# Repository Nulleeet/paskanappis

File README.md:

# paskanäppis
60%(ish)keyboard with ISO kc_nubs and f-row - so its really like 70% or 75%, or between, I dont know. I call it either paskanäppis or 60ish.

This is my learning opportunity to make and design my own keyboard.
Planning to use [kicad](https://www.kicad.org), [qmk](https://qmk.fm), [via](https://www.caniusevia.com) and/or [vial](https://get.vial.today) and [Keyboard PCB Builder](https://kb.xyz.is) and some 3d software (still planning what to use), and 3dprint case, for starters.
Maybe use [plate & case builder](http://builder.swillkb.com) to make acrylic case?

I tried already earlier to do this without Promicro and Elite-C, but I failed it and now the files are gone due to my hdd exploding.

So now Im going to upload everything here while im going forward with this. You can suggest and help me with everything, if you see some flaws or anything.

Layout made in [KLE](http://www.keyboard-layout-editor.com).

TO-DO list:

- Traces in kicad ✔️
- Reposition Elite-C ✔️ used promicro instead and redid traces
- make qmk/via/vial code
- Design a 3d printable case
- ('Design' a acrylic case?)
- figure out how to mounting holes and screws when at that point.✔️
- RGB? 🤔

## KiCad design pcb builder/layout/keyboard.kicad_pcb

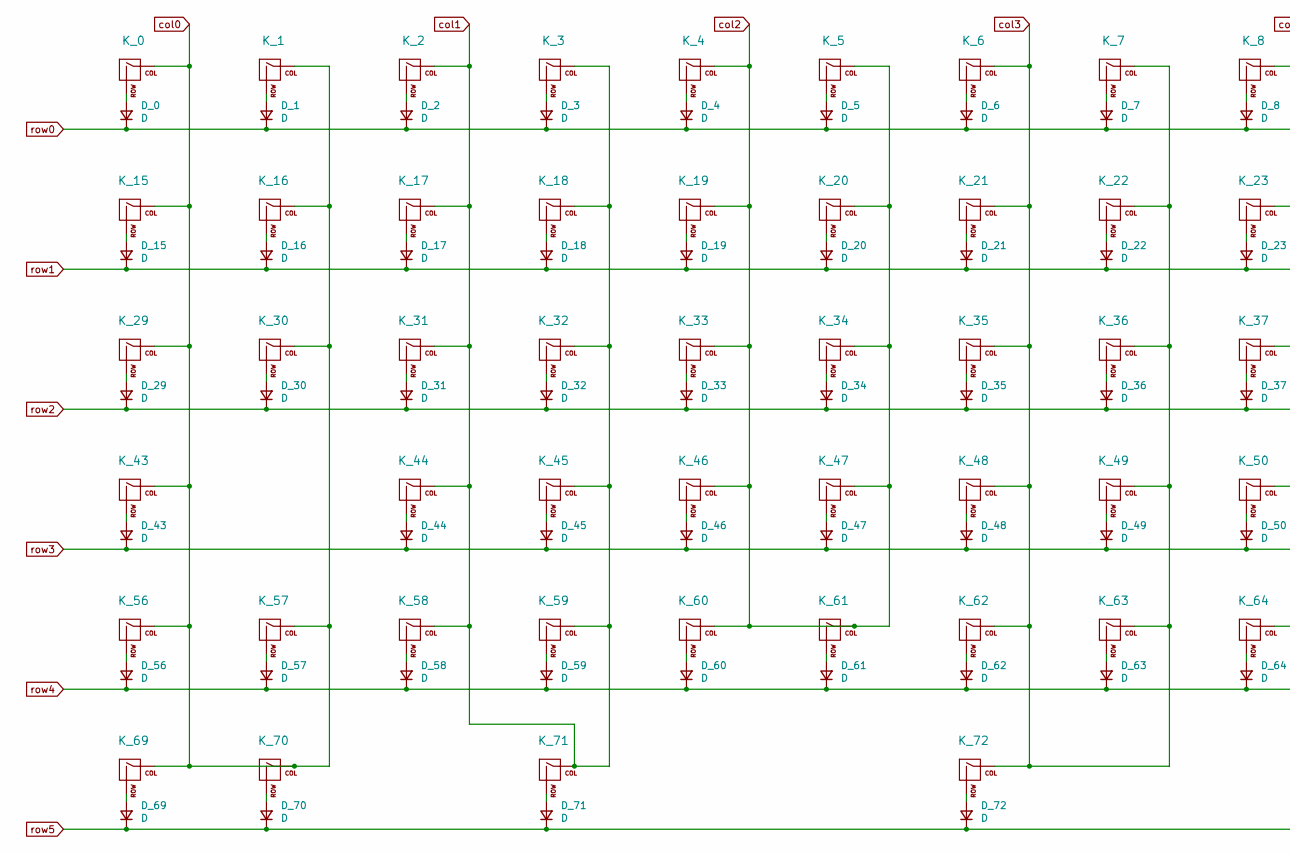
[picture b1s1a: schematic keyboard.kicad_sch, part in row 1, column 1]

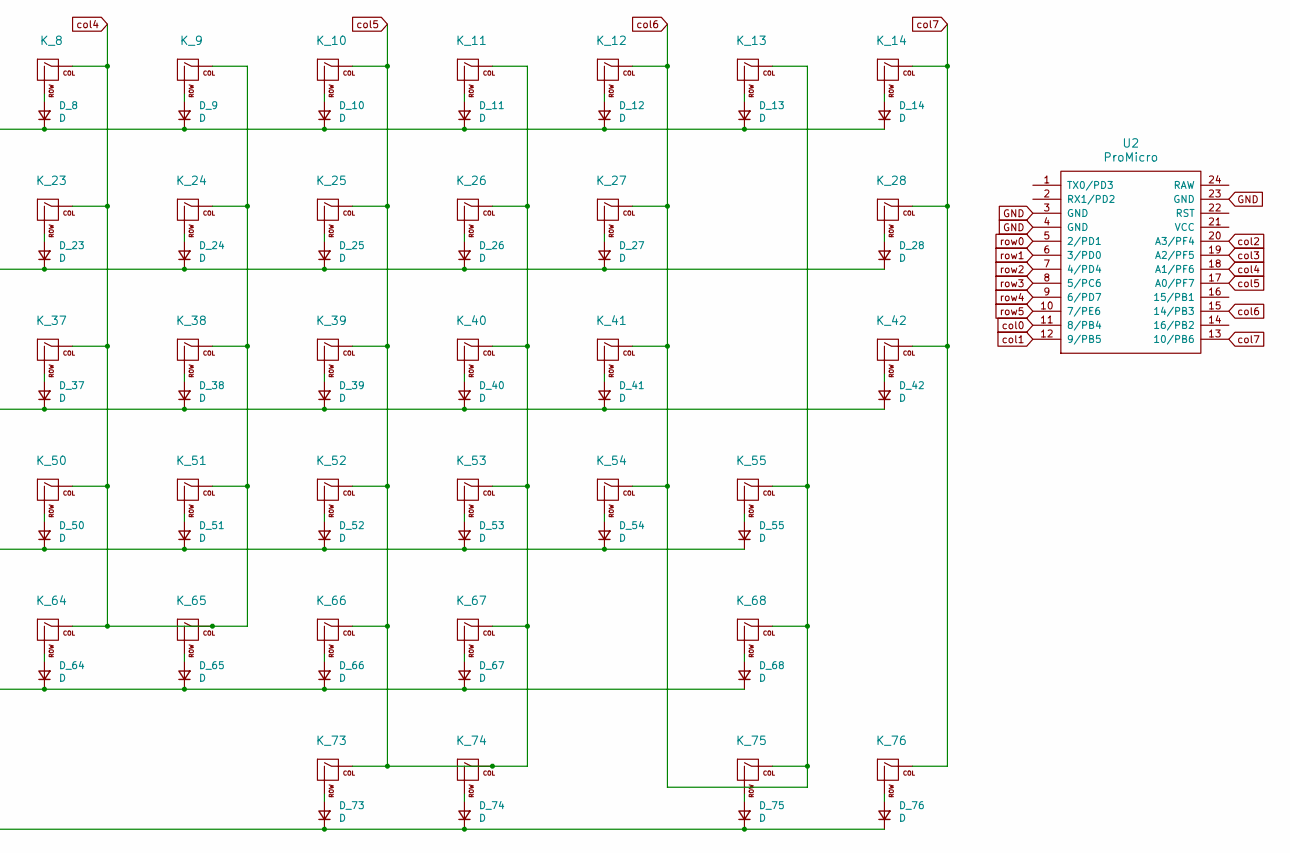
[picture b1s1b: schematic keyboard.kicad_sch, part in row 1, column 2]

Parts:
D_0, D_1, D_2, D_3, D_4, D_5, D_6, D_7, D_8, D_9, D_10, D_11, D_12, D_13, D_14, D_15, D_16, D_17, D_18, D_19, D_20, D_21, D_22, D_23, D_24, D_25, D_26, D_27, D_28, D_29, D_30, D_31, D_32, D_33, D_34, D_35, D_36, D_37, D_38, D_39, D_40, D_41, D_42, D_43, D_44, D_45, D_46, D_47, D_48, D_49, D_50, D_51, D_52, D_53, D_54, D_55, D_56, D_57, D_58, D_59, D_60, D_61, D_62, D_63, D_64, D_65, D_66, D_67, D_68, D_69, D_70, D_71, D_72, D_73, D_74, D_75, D_76: D; D_SOD-123
K_0, K_1, K_2, K_3, K_4, K_5, K_6, K_7, K_8, K_9, K_10, K_11, K_12, K_13, K_14, K_15, K_16, K_17, K_18, K_19, K_20, K_21, K_22, K_23, K_24, K_25, K_26, K_27, K_30, K_31, K_32, K_33, K_34, K_35, K_36, K_37, K_38, K_39, K_40, K_41, K_44, K_45, K_46, K_47, K_48, K_49, K_50, K_51, K_52, K_53, K_54, K_57, K_58, K_59, K_60, K_61, K_62, K_63, K_64, K_65, K_66, K_67: KEYSW; MX-1U-NoLED
K_28: KEYSW; MX-2U-NoLED
K_29, K_56, K_69, K_70, K_71, K_73, K_74, K_75, K_76: KEYSW; MX-1.25U-NoLED
K_42, K_43: KEYSW; MX-1.75U-NoLED
K_55: KEYSW; MX-2.25U-NoLED
K_68: KEYSW; MX-2.75U-NoLED
K_72: KEYSW; MX-6.25U-NoLED
U2: ProMicro; ArduinoProMicro

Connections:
GND: U2.3 (GND), U2.4 (GND), U2.23 (GND)
unnamed: D_0.2 (A), K_0.2 (ROW)
unnamed: D_1.2 (A), K_1.2 (ROW)
unnamed: D_2.2 (A), K_2.2 (ROW)
unnamed: D_3.2 (A), K_3.2 (ROW)
unnamed: D_4.2 (A), K_4.2 (ROW)
unnamed: D_5.2 (A), K_5.2 (ROW)
unnamed: D_6.2 (A), K_6.2 (ROW)
unnamed: D_7.2 (A), K_7.2 (ROW)
unnamed: D_8.2 (A), K_8.2 (ROW)
unnamed: D_9.2 (A), K_9.2 (ROW)
unnamed: D_10.2 (A), K_10.2 (ROW)
unnamed: D_11.2 (A), K_11.2 (ROW)
unnamed: D_12.2 (A), K_12.2 (ROW)
unnamed: D_13.2 (A), K_13.2 (ROW)
unnamed: D_14.2 (A), K_14.2 (ROW)
unnamed: D_15.2 (A), K_15.2 (ROW)
unnamed: D_16.2 (A), K_16.2 (ROW)
unnamed: D_17.2 (A), K_17.2 (ROW)
unnamed: D_18.2 (A), K_18.2 (ROW)
unnamed: D_19.2 (A), K_19.2 (ROW)
unnamed: D_20.2 (A), K_20.2 (ROW)
unnamed: D_21.2 (A), K_21.2 (ROW)
unnamed: D_22.2 (A), K_22.2 (ROW)
unnamed: D_23.2 (A), K_23.2 (ROW)
unnamed: D_24.2 (A), K_24.2 (ROW)
unnamed: D_25.2 (A), K_25.2 (ROW)
unnamed: D_26.2 (A), K_26.2 (ROW)
unnamed: D_27.2 (A), K_27.2 (ROW)
unnamed: D_28.2 (A), K_28.2 (ROW)
unnamed: D_29.2 (A), K_29.2 (ROW)
unnamed: D_30.2 (A), K_30.2 (ROW)
unnamed: D_31.2 (A), K_31.2 (ROW)
unnamed: D_32.2 (A), K_32.2 (ROW)
unnamed: D_33.2 (A), K_33.2 (ROW)
unnamed: D_34.2 (A), K_34.2 (ROW)
unnamed: D_35.2 (A), K_35.2 (ROW)
unnamed: D_36.2 (A), K_36.2 (ROW)
unnamed: D_37.2 (A), K_37.2 (ROW)
unnamed: D_38.2 (A), K_38.2 (ROW)
unnamed: D_39.2 (A), K_39.2 (ROW)
unnamed: D_40.2 (A), K_40.2 (ROW)
unnamed: D_41.2 (A), K_41.2 (ROW)
unnamed: D_42.2 (A), K_42.2 (ROW)
unnamed: D_43.2 (A), K_43.2 (ROW)
unnamed: D_44.2 (A), K_44.2 (ROW)
unnamed: D_45.2 (A), K_45.2 (ROW)
unnamed: D_46.2 (A), K_46.2 (ROW)
unnamed: D_47.2 (A), K_47.2 (ROW)
unnamed: D_48.2 (A), K_48.2 (ROW)
unnamed: D_49.2 (A), K_49.2 (ROW)
unnamed: D_50.2 (A), K_50.2 (ROW)
unnamed: D_51.2 (A), K_51.2 (ROW)
unnamed: D_52.2 (A), K_52.2 (ROW)
unnamed: D_53.2 (A), K_53.2 (ROW)
unnamed: D_54.2 (A), K_54.2 (ROW)
unnamed: D_55.2 (A), K_55.2 (ROW)
unnamed: D_56.2 (A), K_56.2 (ROW)
unnamed: D_57.2 (A), K_57.2 (ROW)
unnamed: D_58.2 (A), K_58.2 (ROW)
unnamed: D_59.2 (A), K_59.2 (ROW)
unnamed: D_60.2 (A), K_60.2 (ROW)
unnamed: D_61.2 (A), K_61.2 (ROW)
unnamed: D_62.2 (A), K_62.2 (ROW)
unnamed: D_63.2 (A), K_63.2 (ROW)
unnamed: D_64.2 (A), K_64.2 (ROW)
unnamed: D_65.2 (A), K_65.2 (ROW)
unnamed: D_66.2 (A), K_66.2 (ROW)
unnamed: D_67.2 (A), K_67.2 (ROW)
unnamed: D_68.2 (A), K_68.2 (ROW)
unnamed: D_69.2 (A), K_69.2 (ROW)
unnamed: D_70.2 (A), K_70.2 (ROW)
unnamed: D_71.2 (A), K_71.2 (ROW)
unnamed: D_72.2 (A), K_72.2 (ROW)
unnamed: D_73.2 (A), K_73.2 (ROW)
unnamed: D_74.2 (A), K_74.2 (ROW)
unnamed: D_75.2 (A), K_75.2 (ROW)
unnamed: D_76.2 (A), K_76.2 (ROW)
col0: K_0.1 (COL), K_1.1 (COL), K_15.1 (COL), K_16.1 (COL), K_29.1 (COL), K_30.1 (COL), K_43.1 (COL), K_56.1 (COL), K_57.1 (COL), K_69.1 (COL), K_70.1 (COL), U2.11 (8/PB4)
col1: K_2.1 (COL), K_3.1 (COL), K_17.1 (COL), K_18.1 (COL), K_31.1 (COL), K_32.1 (COL), K_44.1 (COL), K_45.1 (COL), K_58.1 (COL), K_59.1 (COL), K_71.1 (COL), U2.12 (9/PB5)
col2: K_4.1 (COL), K_5.1 (COL), K_19.1 (COL), K_20.1 (COL), K_33.1 (COL), K_34.1 (COL), K_46.1 (COL), K_47.1 (COL), K_60.1 (COL), K_61.1 (COL), U2.20 (A3/PF4)
col3: K_6.1 (COL), K_7.1 (COL), K_21.1 (COL), K_22.1 (COL), K_35.1 (COL), K_36.1 (COL), K_48.1 (COL), K_49.1 (COL), K_62.1 (COL), K_63.1 (COL), K_72.1 (COL), U2.19 (A2/PF5)
col4: K_8.1 (COL), K_9.1 (COL), K_23.1 (COL), K_24.1 (COL), K_37.1 (COL), K_38.1 (COL), K_50.1 (COL), K_51.1 (COL), K_64.1 (COL), K_65.1 (COL), U2.18 (A1/PF6)
col5: K_10.1 (COL), K_11.1 (COL), K_25.1 (COL), K_26.1 (COL), K_39.1 (COL), K_40.1 (COL), K_52.1 (COL), K_53.1 (COL), K_66.1 (COL), K_67.1 (COL), K_73.1 (COL), K_74.1 (COL), U2.17 (A0/PF7)
col6: K_12.1 (COL), K_13.1 (COL), K_27.1 (COL), K_41.1 (COL), K_54.1 (COL), K_55.1 (COL), K_68.1 (COL), K_75.1 (COL), U2.15 (14/PB3)
col7: K_14.1 (COL), K_28.1 (COL), K_42.1 (COL), K_76.1 (COL), U2.13 (10/PB6)
row0: D_0.1 (K), D_1.1 (K), D_2.1 (K), D_3.1 (K), D_4.1 (K), D_5.1 (K), D_6.1 (K), D_7.1 (K), D_8.1 (K), D_9.1 (K), D_10.1 (K), D_11.1 (K), D_12.1 (K), D_13.1 (K), D_14.1 (K), U2.5 (2/PD1)
row1: D_15.1 (K), D_16.1 (K), D_17.1 (K), D_18.1 (K), D_19.1 (K), D_20.1 (K), D_21.1 (K), D_22.1 (K), D_23.1 (K), D_24.1 (K), D_25.1 (K), D_26.1 (K), D_27.1 (K), D_28.1 (K), U2.6 (3/PD0)
row2: D_29.1 (K), D_30.1 (K), D_31.1 (K), D_32.1 (K), D_33.1 (K), D_34.1 (K), D_35.1 (K), D_36.1 (K), D_37.1 (K), D_38.1 (K), D_39.1 (K), D_40.1 (K), D_41.1 (K), D_42.1 (K), U2.7 (4/PD4)
row3: D_43.1 (K), D_44.1 (K), D_45.1 (K), D_46.1 (K), D_47.1 (K), D_48.1 (K), D_49.1 (K), D_50.1 (K), D_51.1 (K), D_52.1 (K), D_53.1 (K), D_54.1 (K), D_55.1 (K), U2.8 (5/PC6)
row4: D_56.1 (K), D_57.1 (K), D_58.1 (K), D_59.1 (K), D_60.1 (K), D_61.1 (K), D_62.1 (K), D_63.1 (K), D_64.1 (K), D_65.1 (K), D_66.1 (K), D_67.1 (K), D_68.1 (K), U2.9 (6/PD7)
row5: D_69.1 (K), D_70.1 (K), D_71.1 (K), D_72.1 (K), D_73.1 (K), D_74.1 (K), D_75.1 (K), D_76.1 (K), U2.10 (7/PE6)

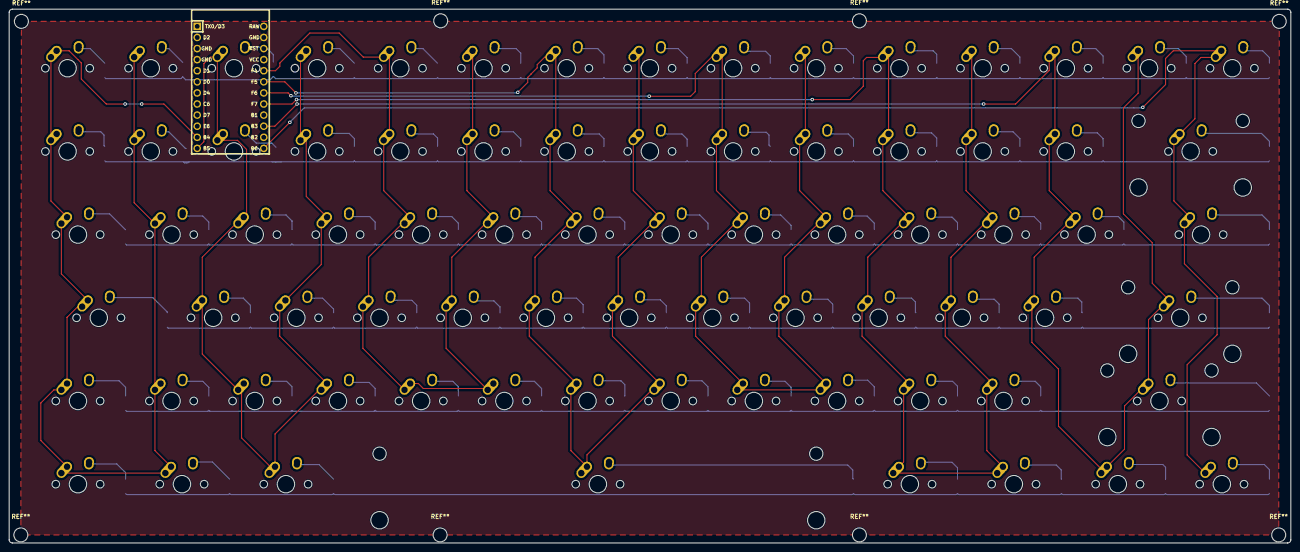
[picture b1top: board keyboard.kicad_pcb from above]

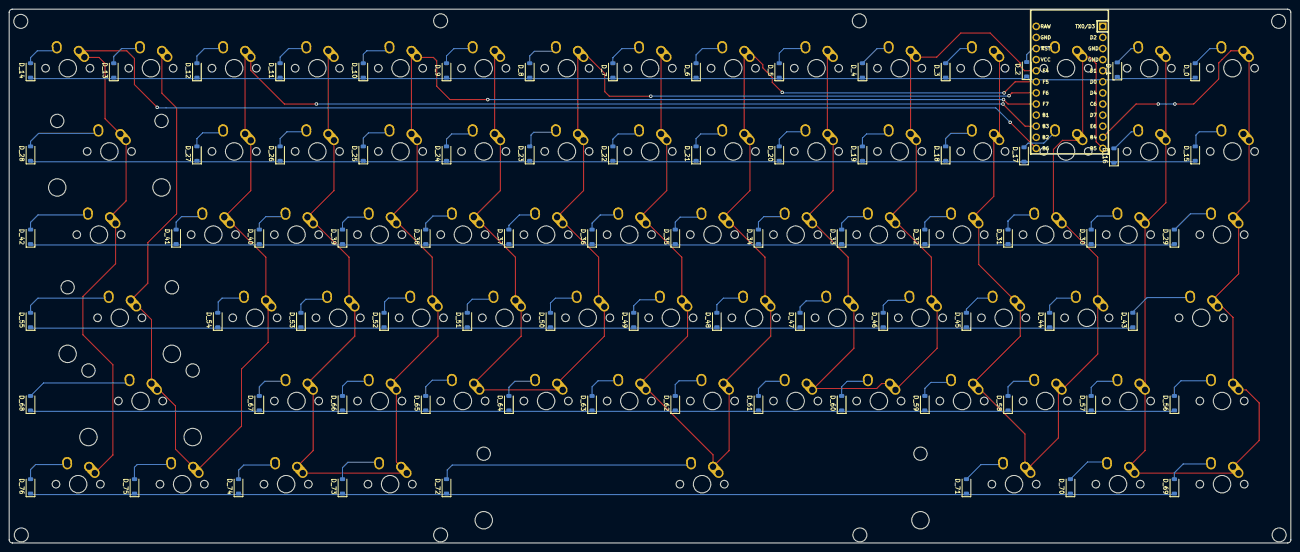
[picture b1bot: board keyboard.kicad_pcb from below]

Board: 2 copper layers, 293.5 x 122.2 mm, 155 parts (77 on the bottom side), 92 nets.

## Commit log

2023-06-17 KLE was made
    ["ESC","F1","F2","F3","F4","F5","F6","F7","F8","F9","F10","F11","F12","volUP","volD"],
    ["§","!\n1","@\n2","#\n3","$\n4","%\n5","&\n6","/\n7","(\n8",")\n9","=\n0","-\n_","+\n=",{w:2},"BACKSPACE"],
    [{w:1.25},"TAB","Q","W","E","R","T","Y","U","I","O","P","Å","^",{w:1.75},"|\n\\"],
    [{w:1.75},"CAPS","A","S","D","F","G","H","J","K","L","Ö","Ä",{w:2.25},"ENTER"],
    [{w:1.25},"SHIFT","<>|","Z","X","C","V","B","N","M",",",".","-",{w:2.75},"SHIFT"],
    [{a:6,w:1.25},"CTRL",{a:4,w:1.25},"\nWIN\n\n\n\n\nSUPR",{a:6,w:1.25},"ALT",{a:4,w:6.25},"SPACE\n\n\n\n\n\nSPACE",{a:6,w:1.25},"ALT",{a:4,w:1.25},"\nWIN\n\n\n\n\nSUPR",{a:6,w:1.25},"MENU",{w:1.25},"CT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
2023-06-17 Update README.md
    kekw
2023-06-17 Update README.md
    testing
2023-06-17 Update README.md
    test
2023-06-17 wrong directory
2023-06-17 SUPR -> SUPER
2023-06-17 testi
2023-06-17 project start
    started new kicad project
2023-06-17 Add submodules
2023-06-17 libraries added
2023-06-17 Add keebio submodules
2023-06-17 more submodules
2023-06-17 keebio modulkes
2023-06-17 Doing something in kicad.
    IDK. Tried first to make layout on kicad, it was taking ages so decided to try and just add promicro from keebio to pcb builder's already made stuff. But it doesnt want to update it to pcb from schem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
2023-06-17 submoduling all folders KEKW
2023-06-17 submoduling erry folders KEKW
2023-06-17 adding elite-c
    It doesnt add Elite-C from keebio to PCB Editor.
2023-06-17 successfully added elite-c
    still need to make routes
2023-06-18 rounded pcb corners
2023-06-18 traced diodes and switches
    Need to reposition elite-c and do traces for rows and cols to elite-c.
2023-06-18 retraced everything for promicro.
    Thanks Keepo for help. Hope it works now.
2023-06-18 ei mitää nähtävää
2023-06-18 added some mounting holes for m3 screws.
2023-06-18 checkmark mounting holes
2023-06-18 pcb 3d render pics from kicad
2023-06-18 filled zone GND
